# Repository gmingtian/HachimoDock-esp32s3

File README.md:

# HachimoDock-esp32s3

ESP32-S3 A4 载板适配版：**三颗按键＋四向摇杆（支持按下）**，320×240 横屏桌宠与离线小游戏。

本仓库由 [gmingtian](https://github.com/gmingtian) 维护，基于 **Yizheng Wang / [YizhengWw/HachimoDock](https://github.com/YizhengWw/HachimoDock)**。这是非官方修改版，保留原项目署名、[许可证](LICENSE)及[第三方声明](THIRD_PARTY_NOTICES.md)，不代表上游背书。

[下载 0.1.203（预发布）](https://github.com/gmingtian/HachimoDock-esp32s3/releases/tag/v0.1.203-s3-a4-r16d) · [安装与恢复](docs/INSTALLATION.md) · [按钮与摇杆](docs/ESP32-S3-A4-Controls.md) · [PCB 与外壳](hardware/README.md) · [兼容性](docs/COMPATIBILITY.md) · [English](README.en.md)

当前发布：客户端 **0.1.203 A4 定制预发布版**；配套固件 **0.7.103-s3-r16d-80m-l320**。Windows x64、Apple 芯片 macOS arm64（13.5+）、Linux x86_64 安装包均已完成原生构建、资源转码和界面启动验证。

## 实物

| A4 焊接板，城市电台 | 装壳整机，桌宠首页 |
| --- | --- |
|  |  |

以上为本机真实照片，保留原图。PCB 已焊接并完成这台设备的装壳使用；照片不替代其他打印材料、模块批次、极限摇杆行程或无线/声学测试。

## 下载

| 文件 | 直达下载 | 说明 |
| --- | --- | --- |
| Windows 客户端 | [Windows x64 安装包](https://github.com/gmingtian/HachimoDock-esp32s3/releases/download/v0.1.203-s3-a4-r16d/HachimoDock-esp32s3_Windows-x64.exe) | NSIS 安装程序 |
| macOS 客户端 | [macOS ARM64 DMG](https://github.com/gmingtian/HachimoDock-esp32s3/releases/download/v0.1.203-s3-a4-r16d/HachimoDock-esp32s3_macOS-arm64.dmg) | Apple 芯片，macOS 13.5+；本地签名、未公证 |
| Linux 客户端 | [Linux x86_64 压缩包](https://github.com/gmingtian/HachimoDock-esp32s3/releases/download/v0.1.203-s3-a4-r16d/HachimoDock-esp32s3_Linux-x64.tar.gz) | Ubuntu 24.04 基线；解压后运行 `launch.sh`，系统依赖见安装说明 |
| PCB 与完整外壳 | [A4 硬件及 R4.4 外壳包](https://github.com/gmingtian/HachimoDock-esp32s3/releases/download/v0.1.202-s3-a4-r16c/HachimoDock-A4-hardware-R4.4.zip) | Gerber、KiCad、BOM、接线表、上下盖 STL / STEP 及操作件 |
| 单独键帽与摇杆 | [6 件独立 STL](https://github.com/gmingtian/HachimoDock-esp32s3/releases/download/v0.1.202-s3-a4-r16c/HachimoDock-A4-keycaps-joystick-STL.zip) | 三个键帽＋摇杆外帽、连接件、盖板；mm，100% 比例 |
| S3 应用升级 | [r16d OTA 固件](https://github.com/gmingtian/HachimoDock-esp32s3/releases/download/v0.1.203-s3-a4-r16d/HachimoDock-S3-A4-r16d-OTA.bin) | 已有匹配 A4 分区布局的设备应用升级 |
| S3 首次刷写 / 恢复 | [r16d 干净全量包](https://github.com/gmingtian/HachimoDock-esp32s3/releases/download/v0.1.203-s3-a4-r16d/HachimoDock-S3-A4-r16d-factory.zip) | 首次改刷或完整恢复；会替换配置与资源，按包内说明刷写 |

[全部附件、游戏与源码](https://github.com/gmingtian/HachimoDock-esp32s3/releases/tag/v0.1.203-s3-a4-r16d) · [SHA256SUMS 校验文件](https://github.com/gmingtian/HachimoDock-esp32s3/releases/download/v0.1.203-s3-a4-r16d/SHA256SUMS) · [安装与恢复说明](docs/INSTALLATION.md)。本版修复及验证范围见[发布说明](docs/RELEASE-0.1.203.md)。

## 当前功能

- **原生 320×240 合成、80MHz SPI**，保留动画与会话气泡、中文菜单及局部刷新优化。80MHz 已在这台设备试用正常，其他屏幕或长排线需自行验收；素材帧率上限不等于整机实测帧率。
- **A4 官方按钮/摇杆操作方式**：摇杆导航，1 键确认及按住语音，2 键组件中心，3 键返回。已移除早期纯三键替代摇杆的软件操作模式。
- **组件和游戏**：恢复云端跳一跳、像素方块、蛙蛙养成；加入离线人机五子棋、中国象棋。象棋支持简单/普通/困难和全部棋种的合法落点光标引导，选中棋子后可用摇杆跳到候选位置。
- **象棋 r16c 优化**：只缩短 AI 分片等待，保持搜索深度、工作量和评分；36 个变化局面对比结果一致。固定开局困难档单次设备对比约 4.60 秒→2.20 秒，不能代表所有局面的耗时，详见[验证记录](docs/ESP32-S3-r16c-Xiangqi-Speed.md)。游戏独立在设备运行，无需电脑计算。
- **配套客户端**：Agent 会话、形象及组件同步、USB / 局域网 Wi-Fi、按键配置、语音服务入口。联网服务仍需相应账号、凭据与网络；Linux 跨应用自动填字有限制。
- **升级保护**：S3 芯片与项目名校验，防止误刷 P4 镜像；OTA 事务及回滚机制。升级前仍应核对目标板与附件校验值。

## 硬件和操作

目标为 ESP32-S3 N16R8（16MiB Flash / 8MiB PSRAM）、240×320 ST7789 横装为 320×240、INMP441 和 MAX98357A。屏幕正视排线在左侧，使用 A4 PCB 对应接线。

| 接口 | GPIO |
| --- | --- |
| SW1 / SW2 / SW3 | 39 / 38 / 0 |
| 摇杆 X / Y / 按下 | 1 / 2 / 8 |
| LCD CLK / MOSI / RST / DC / CS / BL | 21 / 47 / 45 / 40 / 41 / 42 |
| 麦克风 WS / BCLK / DIN | 4 / 5 / 6 |
| 功放 DOUT / BCLK / LRCK | 7 / 15 / 16 |

GPIO0 上电或复位时请松开。按键可在客户端配置，具体游戏以屏幕提示为准。五子棋：1 开始/落子/重开，2 悔棋，3 退出。象棋：1 选棋/落子，2 优先取消选中、否则悔棋，3 退出；上下选择难度。

[硬件交付索引](hardware/README.md)列出 **A4 Gerber、KiCad 原理图/PCB、自包含库、BOM、接线表、R4.4 上下盖 STL 与 STEP，以及单独的三键帽和摇杆帽 A/B/盖板 STL**。早期 A0–A3、R0–R4.3 与试装骨架属于过程资料，请勿混用制造文件。

## 安装和开发

从 [Release](https://github.com/gmingtian/HachimoDock-esp32s3/releases/tag/v0.1.203-s3-a4-r16d) 选择对应系统客户端及 S3 固件附件，先阅读[安装与恢复](docs/INSTALLATION.md)。安装客户端不会自动刷机；应用镜像不能写入 0x0，首次完整刷机与保留资源的 OTA 升级用途不同。

开发依赖与命令见 [S3 构建/接线](docs/ESP32-S3-Linux.md)、[Linux 客户端](pc/docs/linux-native.md)及 `pc/` 工程。Docker 是可选构建方式，使用本机 Node、Rust、ESP-IDF 也可完成相应构建。

本版本针对 A4 S3 硬件；P4 共用的游戏核心不等于本包可直接刷入 P4。触屏专用组件不因摇杆适配而具备触屏能力。语音采用当前 S3 半双工路径，未声明经声学校准的全双工/AEC。完整边界见[兼容性](docs/COMPATIBILITY.md)。

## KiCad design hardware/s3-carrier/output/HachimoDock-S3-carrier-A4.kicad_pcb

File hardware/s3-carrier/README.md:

# HachimoDock ESP32-S3 一体底板 A4

当前推荐为 **A4 PCB＋R4.4 外壳＋A4 按钮/摇杆固件 r16c**。这台板已完成焊接并装壳使用，真实照片见[项目首页](../../README.md#实物)。软件已启用 GPIO1/2/8 摇杆并恢复官方按钮操作，见[控件说明](../../docs/ESP32-S3-A4-Controls.md)。原导出图纸里“摇杆预留/固件未启用”是早期文字，PCB 网络与 Gerber 不变。

[硬件交付索引](../README.md)列出当前制造文件、可编辑源和 SHA-256。A0–A3 及早期外壳输出只作历史记录，不与 A4 制造包混用。R4.4 采用 H3/H4 热熔铜螺母固定、H1 塑料定位；下文原壳 H1/H4 螺丝及历史 A2/A3 结构说明不适用于当前外壳装配。

本次只更新交付说明，没有重新绘制/布线或修改 Gerber。原设计检查报告保留其生成时的“工程样板/实物未验证”状态；本机后续焊接、显示、操作与装壳反馈单独记录，不据此改写原审计结论或声称批量生产认证。其他模块批次、极限运动、射频与声学仍需验证。

[下载 A4 Gerber 制造文件](output/HachimoDock-S3-carrier-A4-Gerber.zip) · [BOM](output/BOM.csv) · [接线表](output/connections.csv) · [电气核对](output/electrical-audit.md) · [平面间隙核对](output/mechanical-audit.md)

[原理图 PDF](output/HachimoDock-S3-carrier-A4-schematic.pdf) · [可编辑 KiCad 原理图](output/HachimoDock-S3-carrier-A4.kicad_sch) · [原理图与 PCB 网表比对](output/schematic-audit.json)

Gerber ZIP 的 SHA256 为 `f37d6a4aacb843249476b656e248e3e576f963c258f840ecbc87fd694797cb69`，对应 PCB SHA256 为 `3ea5f653f6bf27bdb09c90290e1f22ae493803e0c346911ff89b9b5f40b8624e`；逐文件校验见 `output/manufacturing-export.json`。本次装配说明及渲染修订未改变该 PCB 或 Gerber。

**A4 在 A3 上增加 JP1 功放增益跳线座。** 所有原有模块、屏幕接口、按键、摇杆、板框及孔位保持 A3 坐标，仅增加三针排针及 GAIN 网络，并重新布线和检查。已上传嘉立创的 A3 Gerber 不包含此功能，须替换为 `HachimoDock-S3-carrier-A4-Gerber.zip`。

**A3 修正了 A2 的 H3 螺丝头与屏幕插头空间不足问题。** 原安装孔及整体布局不动，仅将 J1 屏幕排针向上移动1.6mm，Y=32.6→31.0mm。按杜邦插头最大22×3mm、固定螺丝头最大Ø6mm核算，上侧ESP32排母/下侧螺丝头分别留约0.54/0.56mm平面余量。A2压缩包仅作历史备份，其2.14mm上侧间隙和缺少螺丝头的检查不能用于A3。实际排母宽度、螺丝外径、高度和装配仍需核准。

保留原版 V1.2 板框、五个安装孔、三个机械轴与 YA13S 摇杆的位置，改为一块底板承载果云 ESP32-S3、MAX98357A 和圆形 INMP441。板框约 **73.47 × 69.47 mm**，双层、1.6 mm；现有 LCD、麦克风、功放与三个按键的 GPIO 保持代码定义。

**采用现有 GPIO 直连接线：删除 A0 的 Q1、Q2、R1、R2、R3，BL 直接接 GPIO42；功放 GAIN 接 JP1 中间针，通过一个跳线帽选增益；SPK+/SPK− 只在功放模块上接喇叭，底板不设置对应焊盘、孔和网络。** 不新增分立电阻、电容、三极管或 MOS 管，保留现成模块上的原有器件。旧 A0 压缩包另外保留，不能与 A2 混用装配说明。

**A2 在此基础上旋转果云板 180°，再向左侧 USB 端平移 3 mm，USB 朝向原版同一侧并靠近板边。重新映射的是底板排母的物理位置；每根编号引脚对应的电源/GPIO 网络不变。A1 开发板不能在旧底板上直接反插。** A0、A1 压缩包及输出另行保留。

## USB 位置方案选择

比较了两种平面布局：旋转后 USB 朝左，以及保持原方向、平移后 USB 朝右；两种都按接口端贴近板边安排。最终选择 **旋转后 USB 朝左的 A2**，因为 USB 方向与原版一致，LCD 的 CLK/MOSI 引脚到屏幕插针的直线距离更短。不旋转的右侧方案有更短的音频线，但会把外壳 USB 孔换到另一侧；当前网格布线器也未完成该比较方案，不能据此断定人工布线不可行。

`output/usb-options.json` 记录两种朝向的引脚距离及判断依据。这些距离是几何直线下限，不是最终铜箔长度，也不代表实测速率。A3 的实际布线单独通过原生 DRC。

按当前参考封装包络，USB 端外形到达底板左侧 **X≈−0.525 mm**，约外伸 0.5 mm；它不是实测 USB 金属接口面的坐标。果云板两个 USB 接口的位置、高度、插头壳体及原壳开孔仍需核准。即使方向相同，也不能承诺直接对准原 USB 孔；后续 STL 按实际接口做开孔和插头让位。用于桌面客户端连接的是原生 USB 口，不能把另一个串口转换接口视为完全相同的通信口。

天线随开发板转到右侧，禁布区扩大到右板边。参考原壳的历史装配仅使用 H1、H4 两处固定，H2 不安装螺钉；若后续结构确需使用靠近天线的 H2，应采用与孔位及结构匹配的尼龙等非金属紧固件。不要将金属件、屏幕背板和线缆压在天线附近。Wi-Fi 性能尚未经过实物验证。

为保持原板框、五孔和 USB 靠边，当前禁布区没有实现天线周围全方向 15mm 净空，天线下方仍有底板基材。它是明确保留的布局限制，不能把两层无铜和尼龙螺钉等同于完全满足 RF 推荐布局；[乐鑫的天线布置指南](https://docs.espressif.com/projects/esp-hardware-design-guidelines/en/latest/esp32s3/pcb-layout-design.html#general-principles-of-pcb-layout-for-modules-positioning-a-module-on-a-base-board)要求在成品中验证吞吐和距离。

## 布局锁定与本次优化

板框、五个安装孔、SW1/SW2/SW3 和原版 YA13S 的坐标、机械孔径、间距及方向锁定原版；保留原版约14mm 3D打印圆帽，整体布局不再调整。封装焊盘与孔位逐个比对原源文件。摇杆金属脚的铜焊盘仅缩小0.2mm以满足板边间距，原钻孔与机械定位不变。

J1 位于 Y=31.0mm，麦克风中心仍为 (46,42.1)mm。屏幕插头按**最大22×3mm**的8P杜邦外壳预留，与果云下排排母的平面间隙约**0.54mm**，与H3的Ø6mm螺丝头约**0.56mm**，与麦克风包络间隙**2.60mm**；麦克风至右侧键帽预留约**1.07mm**。这些数值使用规划包络，实际连接器或螺丝超出该规格时需重新核对，不能只看金属针或钻孔间距。

五个原固定孔均保留。**参考原壳采用中排左右 H1、H4 两处螺丝固定；中排中央 H3 用于定位/支撑，不安装螺丝，H2、H5 同样不要求安装螺丝。** H1/H4 的坐标分别约为 (11.041,36.003)mm 和 (61.056,36.027)mm，H3 约为 (36.044,36.060)mm。

原五孔周围半径3.5mm的两层铜、走线及过孔禁布区继续保留。检查报告中的五处Ø6mm螺丝头是保守包络假设，不是五颗螺丝的装配要求；H3无螺丝也不代表可以忽略外壳定位柱的实际尺寸。先装实际使用的固定螺丝，再插开发板和音频模块。原版资料列出两颗 M2.5×6 螺丝及两枚 M2.5×4×3.5 热熔铜螺母；具体安装深度和孔位仍须与实际外壳核对。

功放的3V3馈线和地线分别直接连开发板电源脚，避免刻意经麦克风或屏幕串接。两层已填充GND铜，避开右上天线区并去掉孤岛，屏幕地附近增加接地过孔；新增元件仅有 JP1 三针排针及一个跳线帽，没有增加电阻、电容或有源器件。铺铜改善返回路径，不能替代供电容量和音频噪声实测。

摇杆活动区为新增模块/插头保守预留R15mm，**不是帽子直径，也不是实测运动边界**。厂家机械图给出总角60°，规划再考虑角度公差。摇杆帽高于底板元件的高度差有助于避免干涉，但原版摇杆与右侧键帽的完整运动、按压及线缆/屏幕三维间隙仍待核对；不因保守俯视投影相交而移动原版控制器件，也不声称已完成三维无干涉验证。

## 工程文件

- `output/HachimoDock-S3-carrier-A4.kicad_pcb`：主设计，已运行 KiCad 9 原生 DRC。
- 同名 `.kicad_pro`、`fp-lib-table`、`S3_Carrier.pretty/`：工程规则和自包含封装库，应一起打开。
- `output/HachimoDock-S3-carrier-A4.epro2`：嘉立创专业版 PCB 交换文件。焊盘、网络、孔、走线坐标已程序比对，铺铜包含天线角及五个螺丝头的让位；**本次未完成编辑器导入验证，它不是本次DRC的对象，也未转换KiCad原生天线/螺丝头禁布规则**。请以KiCad主设计为准，导入后必须重新设置这些规则、检查铺铜并运行DRC。
- `output/connections.csv`：逐焊盘网络表；`design.json`：全部坐标及布局边界。
- `output/validation.json`、`drc.json`：检查结果；`pcb-preview.png`：按真实坐标绘制的布局与布线图。
- `output/electrical-audit.md/json`：直接从最终 KiCad PCB 焊盘读取的 15 路固件信号与电源核对表，包含当前代码和 PCB 的校验值；`audit-fault-checks.json` 记录六种故意错误均被检出（新增增益接错和跳线中心脚接错）。
- `output/mechanical-audit.md/json`：插头、排母、模块与键帽的尺寸间隙，以及摇杆运动检查的边界。
- `output/drc-attestation.json`：原生DRC结果与最终PCB、工程规则的校验值绑定；修改任一文件后拒绝沿用旧报告打包。
- `output/assembly-orientation.png/svg`：圆形麦克风正面针序、排母插装方向和屏幕直通排线图。
- `output/assembly-render/`：按PCB坐标及原版STEP帽/键帽生成的装配示意。模块电子元件、USB外观和Z高度是示意值；未显示尺寸未确认的屏幕本体，不是实物照片或三维碰撞验证。

这张历史示意图只展示 H1/H4 两处螺丝；当前 R4.4 以外壳说明为准；俯视、前后视角沿用同一套 PCB 坐标。带外壳的 AI 概念图不作为本工程的尺寸或装配依据。

现已补充**模块级 KiCad 原理图及同源 PDF**：展示底板上的九个功能器件/接口，符号内嵌并附带 `S3_Carrier.kicad_sym` 和 `sym-lib-table`。相同网络标签表示相连；叉号表示该开发板引脚未接入本底板外设，不代表开发板内部没有连接。U1 的电源输出类型表示板载 USB/稳压电路提供电源。

原理图由当前 PCB 连接反向整理，再用 KiCad 原生导出网表，与实际 PCB 的86个电气焊盘、83个唯一编号端子和22个网络比对。JS1的四个金属固定焊脚共用编号0，图中合并为 `CASE_4_TABS`。`#PWR01` 只是5V电源标记，不是新增实物元件。原理图 ERC 检查范围为模块接口，不展开模块内部芯片、电源或模拟电路。

**本次未改动 PCB/Gerber，也未重建符号 UUID 到 PCB 封装的自动关联。** 可以独立查看、编辑原理图；不能未经检查就执行“从原理图更新PCB”，否则可能重新匹配或新增封装。当前对应关系由原生网表比对报告证明，机械与实物验证边界不变。

## 装配与接口

1. 果云 **42 针 N16R8** 使用两条 **2.54 mm 1×21P 排母**，两排中心距 25.4 mm。已买的 1×22P 可裁成 21P；不要买成 44 针开发板的底座。A2 开发板 USB 朝左、天线朝右。先以实物逐一核对丝印与 `connections.csv`，不能照 A1 的朝向插装。
2. 三个轴体和原版 YA13S 摇杆焊在原位置；此封装用于原版裸摇杆，**不能把已买的 PS2 小模块当成同尺寸、同引脚封装直接插入**。
3. MAX98357A 使用一条 **1×7P、2.54 mm 排母**，按 VIN/GND/SD/GAIN/DIN/BCLK/LRC 七针接口对位；VIN 保持用户确认的 **3V3**，SD 接 3V3，GAIN 接 JP1 中间2脚，1脚接3V3，3脚接GND；具体见下方增益表。喇叭直接接模块 SPK+/SPK−，**这两个喇叭端子不与底板连接，SPK− 不接地**。
4. 圆形 INMP441 采用两条 **1×3P、2.54 mm 排母，两排中心距 7.62 mm**，不是一只排距 2.54 mm 的 2×3P 排母。用户提供的商家图标注直径 14 mm、排距 7.62 mm，与封装一致。按已焊排针照片安装：**带字面朝外，长针向下插排母**。从底板元件面看，模块左列从上到下 SD→GPIO6、VDD→3V3、GND→GND；右列从上到下 SCK→GPIO5、WS→GPIO4、L/R→GND。无需拆针或镜像插装。商家图片中的 GPIO14/32/15 是示例，不用于本板。
5. J1 方形焊盘为 1，从底板元件面由左到右为：**GND、VCC、SCL、SDA、RES、DC、CS、BLK**，与用户屏幕照片一致，可用一组 8P 杜邦线 1 对 1 直连。VCC=3V3；SCL=GPIO21、SDA=GPIO47、RES=GPIO45、DC=GPIO40、CS=GPIO41、BLK=GPIO42。插接时先确认两端 GND 对应，不要因从背面看接口而倒序。建议先使用约 5 cm 短线，最终线长与 SPI 时钟需实测。
6. J1 的 BLK 直接接 GPIO42，沿用用户反馈可正常点亮的接法。A3 不含背光功率驱动或外加限流器件；现有屏幕正常点亮的反馈不等于已完成更换屏幕后背光电流的验证。
7. 麦克风中心预留 Ø2 mm 底板声孔；不要用胶堵住声孔。底板声孔不代表模块原孔的直径，也不代替外壳的声学开孔。
8. U1/U2/U3 的排母焊孔均按 Ø1.2 mm 设计，焊盘 Ø1.8 mm。先安装原版固定螺钉，再安装开发板和音频模块。模块下方存在原版固定孔，**排母高度、螺钉头高度、模块背部焊点间隙尚未三维确认**。功放模块的喇叭端子若向下焊接，其焊点同样需与底板保持绝缘间隙。

### 模块尺寸的依据

MAX98357A 在设计与渲染中的平面外形预留为 **20.38×18mm**，来自所采用的参考布局，不能当作已测得的商品外形。用户提供的紫色模块商品图标注约 **17×18mm**；两者应先按针排方向对齐，再核对实际针距、针排到板边距离、焊接方向及插接高度。商品图上的七针顺序与本板相符，但图中未给出全部孔位尺寸。

圆形 INMP441 按商品图的直径14mm、两排中心距7.62mm规划。果云开发板采用参考工程的42针封装。Unvision屏幕的完整机械尺寸尚未确认。排母本体、插入深度、焊点、屏幕背部及线材弯折空间尚未全部实测，不能据渲染图宣称原壳可直接安装。

## JP1 功放增益跳线

使用 **2.54 mm 1×3P 直排针 + 一个两针跳线帽**。从元件面看，JP1 竖向上到下为：1=3V3、2=GAIN、3=GND；1脚为方形焊盘。

| 跳线帽位置 | MAX98357A 在 I²S 模式下的增益 |
|---|---:|
| 1–2（上两针，丝印6dB） | 6 dB，较小 |
| 不装帽（OPEN 9dB） | 9 dB，默认 |
| 2–3（下两针，丝印12dB） | 12 dB，较大 |

该设置来自 [MAX98357A 官方手册第28页表8](https://www.analog.com/media/en/technical-documentation/data-sheets/MAX98357A-MAX98357B.pdf)，不占用ESP32 GPIO，也不用更改固件。它影响所有声音，不仅状态提示音。模块自身若已加装增益电阻或焊桥，需先核对模块线路，不能单凭引脚外观认定实际增益。

**断电后切换，只能装一个跳线帽；禁止同时跨接1–2和2–3，否则会短接3V3与GND。** 跳线帽外形限4×5.5mm，针座与两种插法的合并平面包络按4×8.5mm预留；实际排针/帽高度及外壳可操作空间尚未实物验证。增益座放在功放与麦克风之间，不改变原有部件位置。

## GPIO

| 用途 | GPIO |
|---|---|
| LCD CLK / MOSI / RST / DC / CS / BL | 21 / 47 / 45 / 40 / 41 / 42 |
| INMP441 WS / SCK / SD | 4 / 5 / 6 |
| MAX98357A DIN / BCLK / LRC | 7 / 15 / 16 |
| 原版位置三个按键 SW1 / SW2 / SW3 | 39 / 38 / 0 |
| 摇杆 X / Y / 按下 | 1 / 2 / 8（新增，需固件支持） |

USB GPIO19/20、PSRAM GPIO35/36/37 不接底板外围。摇杆使用 3.3 V 电位器供电。

## 当前验证范围与未决项

已经核对源工程 42 针符号/封装、现有代码 GPIO、原版机械定位、模块平面外形、PCB 焊盘网络和布线。KiCad DRC 不豁免违规；报告随工程提供。摇杆边缘金属脚保留原孔与位置，铜焊盘由 Ø2.0 缩到 Ø1.8 mm，以满足板边间距，孔径仍为 Ø1.2 mm。

以下需完成后才适合冻结生产版：

- 果云及两个音频模块的实际尺寸、排针方向与元件高度；螺钉、USB 插头、原壳的三维装配。
- Unvision 8 针屏幕的板框、固定孔、BL 电路和背光电流。**没有采用另一款屏幕的 54.74 × 81.28 mm 尺寸。**
- 本版功放 VIN、LCD 和麦克风由开发板 3V3 供电。开发板稳压器容量及 Wi-Fi 发射、背光和大音量同时工作时的峰值电流/温升未验证；若供电余量不足，需要调整功放电源或增加独立稳压，不能只凭 DRC 通过就认定供电可用。
- 原板宽度上能摆下这些模块，但仍不能保证沿用原壳后无物理干涉；外壳及屏幕支架未定稿。
- 新摇杆 GPIO1/2/8 的采样、死区、方向映射和去抖需另做固件适配。
- GPIO45沿用当前屏幕RES脚，但它也是S3启动采样脚；更换屏幕后需要检查RES电路的外部拉电平及冷启动稳定性，不能只以现有接线曾点亮代替检查。不要为此擅自改脚位或烧写eFuse。GPIO0按键在复位时按住可能进入下载模式，是该脚的既有行为。

## 来源与使用条件

- [HachimoDock 官方硬件工程](https://oshwhub.com/eda_gqvzlprk/project_cnbmkbjc)：V1.2 板框、孔位、机械轴及摇杆封装，原项目 [YizhengWw/HachimoDock](https://github.com/YizhengWw/HachimoDock)。
- [果云 AI 对话底板参考工程](https://oshwhub.com/ccabcd/ai-dialogue-backplane-based-on-e)：42 针果云及两种音频模块的封装/引脚依据。
- [小智 ESP32-S3 接线说明](https://xiaozhi.me/xz-docs/docs/tutorial-basics/esp32-s3-bread-board-diy-wiring/)：开发板引脚交叉核对。
- [TDK INMP441 数据手册](https://product.tdk.com/system/files/dam/doc/product/sw_piezo/mic/mems-mic/data_sheet/inmp441.pdf)：L/R 接低电平选择左声道，与当前 S3 采集代码一致。
- [YTL 原版 YA13S 数据手册](https://www.lcsc.com/datasheet/C37323748.pdf)：封装机械尺寸和摇杆角度依据。

`reference/` 保留下载的原始工程用于复核，第三方设计与封装的权利、许可和使用条件属于各自原作者；本说明不重新许可第三方内容。改版文件保留原作者归属。上传 Gerber 或完成工程审核不等于打样上电通过；制造与实物验证状态以对应记录为准。

## 重新生成

先运行 `tools/build_design.py`，再运行 `tools/route_board.py`（NumPy、Shapely）；随后以 KiCad 9 的 Python 环境运行 `tools/prepare_kicad.py`，通过 `tools/verify_drc.py --kicad-cli /path/to/kicad-cli` 运行原生DRC并生成校验记录，再运行 `tools/audit_native.py`、`tools/check_audit_faults.py` 和 `tools/check_clearances.py`。最后执行 `tools/export_easyeda.py`、`tools/preview.py`、`tools/assembly_preview.py` 和 `python -m unittest discover -s tests -v`。`tools/package_design.py` 会检查固件代码、PCB、工程规则及各报告的校验值。不要只重新生成设计而省略布线与审核。

仅重新生成原理图时，在仓库根目录执行下列命令；不会修改PCB：

```sh
python3 hardware/s3-carrier/tools/generate_schematic.py
kicad-cli sch export netlist --format kicadxml -o hardware/s3-carrier/output/schematic-netlist.xml hardware/s3-carrier/output/HachimoDock-S3-carrier-A4.kicad_sch
kicad-cli sch erc --format json --severity-all --exit-code-violations -o hardware/s3-carrier/output/schematic-erc.json hardware/s3-carrier/output/HachimoDock-S3-carrier-A4.kicad_sch
kicad-cli sch export pdf --default-font 'Noto Sans CJK SC' -o hardware/s3-carrier/output/HachimoDock-S3-carrier-A4-schematic.pdf hardware/s3-carrier/output/HachimoDock-S3-carrier-A4.kicad_sch
python3 hardware/s3-carrier/tools/schematic_audit.py
python3 -m unittest discover -s hardware/s3-carrier/tests -v
```

网表审计会将原生导出文件中的本机原理图、符号库绝对路径转换为文件名，便于分享；网络连接数据保持原样。

PDF中的中文使用 Noto Sans CJK SC 字体；重新导出后需检查文字与图形排版。修改网络后必须重新导出网表和ERC并比对，不能沿用旧报告。

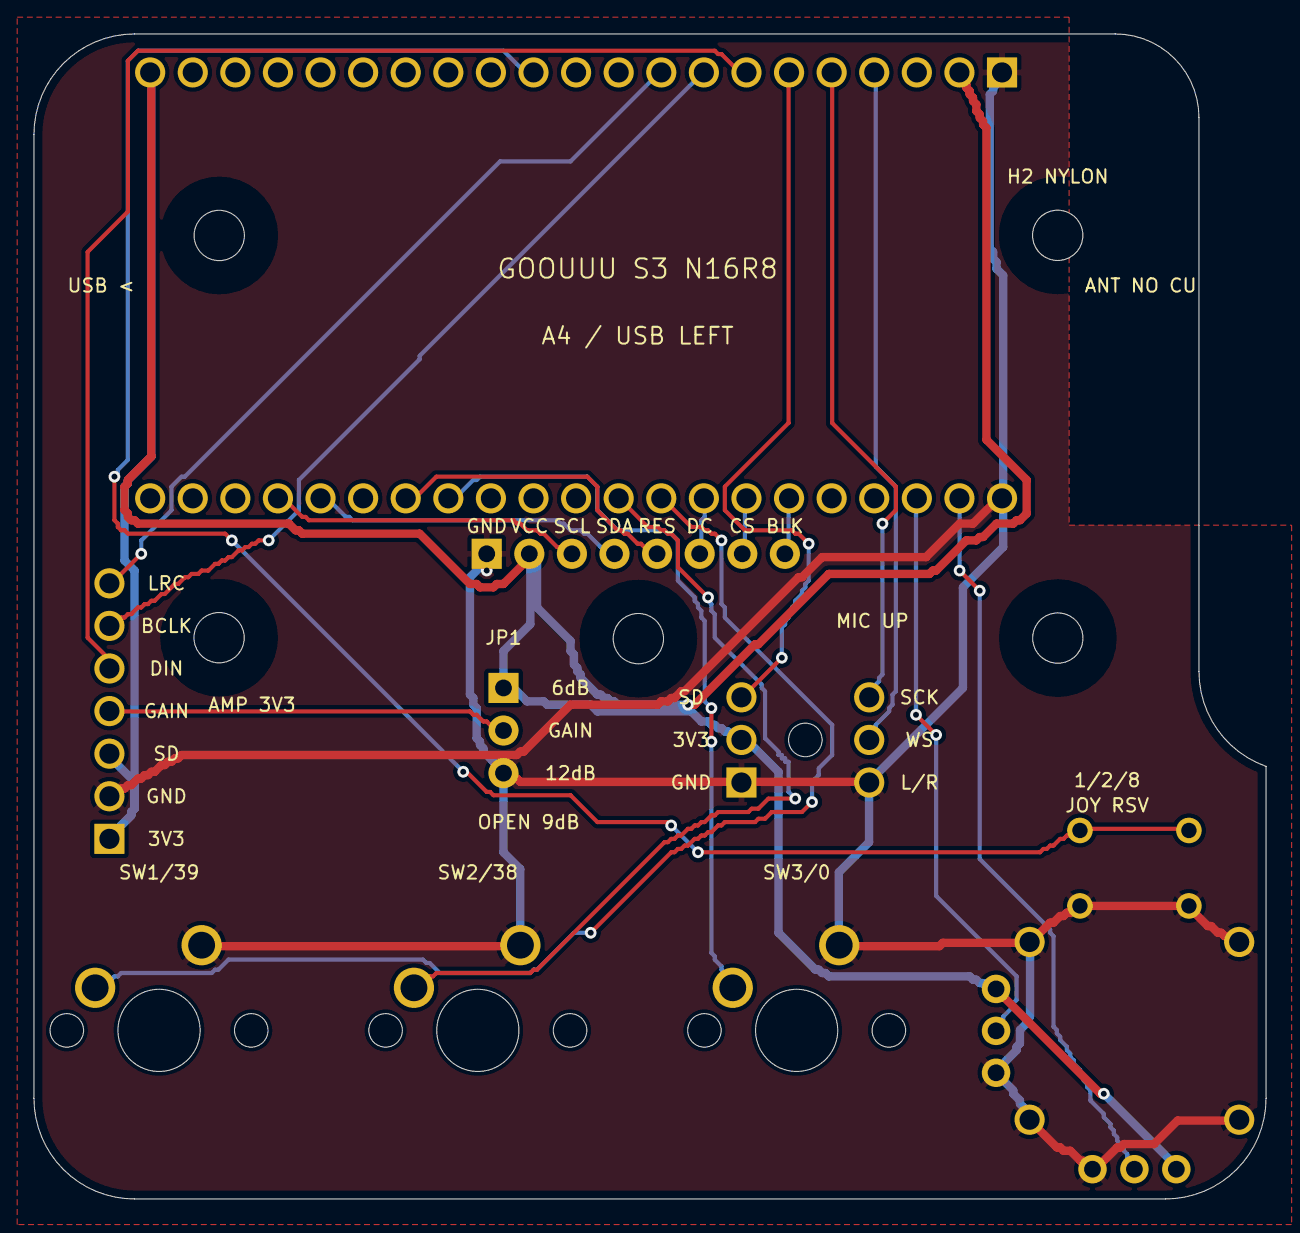
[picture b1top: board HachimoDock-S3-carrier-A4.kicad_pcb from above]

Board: 2 copper layers, 73.5 x 69.5 mm, 14 parts (0 on the bottom side), 21 nets.

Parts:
H1: H1
H2: H2
H3: H3
H4: H4
H5: H5
J1: LCD: GND VCC(3V3) SCL SDA RES DC CS BLK; J1
JP1: AMP GAIN / 1-2=6dB OPEN=9dB 2-3=12dB; JP1
JS1: Original YA13S joystick; JS1
SW1: Original switch / GPIO39; SW1
SW2: Original switch / GPIO38; SW2
SW3: Original switch / GPIO0; SW3
U1: GOOUUU S3 N16R8 / 2x21 sockets; U1
U2: MAX98357A module; U2
U3: Round INMP441 / 14mm; U3

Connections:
+3V3: J1.2, JP1.1, JS1.A1, JS1.B3, U1.2, U1.21, U2.1, U2.3, U3.2
AMP_GAIN: JP1.2, U2.4
GND: J1.1, JP1.3, JS1.0, JS1.A, JS1.A3, JS1.B1, JS1.C, SW1.2, SW2.2, SW3.2, U1.1, U1.22, U2.2, U3.1, U3.4
GPIO0: SW3.1, U1.35
GPIO1: JS1.B2, U1.23
GPIO2: JS1.A2, U1.24
GPIO4: U1.4, U3.5
GPIO5: U1.5, U3.6
GPIO6: U1.6, U3.3
GPIO7: U1.7, U2.5
GPIO8: JS1.B, JS1.D, U1.12
GPIO15: U1.8, U2.6
GPIO16: U1.9, U2.7
GPIO21: J1.3, U1.39
GPIO38: SW2.1, U1.31
GPIO39: SW1.1, U1.30
GPIO40: J1.6, U1.29
GPIO41: J1.7, U1.28
GPIO42: J1.8, U1.27
GPIO45: J1.5, U1.36
GPIO47: J1.4, U1.38

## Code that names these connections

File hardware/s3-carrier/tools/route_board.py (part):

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    def run(self):
        # Reserve the dense small-device ground escapes before signal tracks
        # can enclose them; long routes can use the other copper layer.
        lcd_order={'GPIO21':0,'GPIO47':1,'GPIO45':2,'GPIO40':3,'GPIO41':4,'GPIO42':5}
        # Reserve the paired, via-free LCD escape before wider supply routes
        # occupy the short corridor between devkit sockets and LCD header.
        names=sorted(self.nets,key=lambda n:(0 if n in ['GPIO21','GPIO47'] else
                                            1 if n=='GND' else 2 if n=='+3V3' else
                                            3 if n in lcd_order else 4,lcd_order.get(n,0),n))
        for name in names:
            if name=='GPIO47':continue  # Planned with CLK below.
            pads=[p for p in self.pads if p['net']==name]
            if len(pads)<2:continue
            if name=='GPIO21':
                start=next(p for p in pads if p['ref']=='U1');end=next(p for p in pads if p['ref']=='J1')
                mates=[p for p in self.pads if p['net']=='GPIO47']
                a=next(p for p in mates if p['ref']=='U1');b=next(p for p in mates if p['ref']=='J1')
                offset=round((a['x']-start['x'])/GRID)
                path=self.search(start,end,self.nets[name],(self.nets['GPIO47'],offset))
                self.add_path(path,start,end,name)
                self.add_path([(x+offset,y,1-z) for x,y,z in path],a,b,'GPIO47')
                print('Routed GPIO21 / GPIO47 as opposite-layer LCD pair',flush=True)
                continue
            # Give the amplifier its own feed/return directly to a devkit
            # supply pad instead of daisy-chaining through LCD/microphone.
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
